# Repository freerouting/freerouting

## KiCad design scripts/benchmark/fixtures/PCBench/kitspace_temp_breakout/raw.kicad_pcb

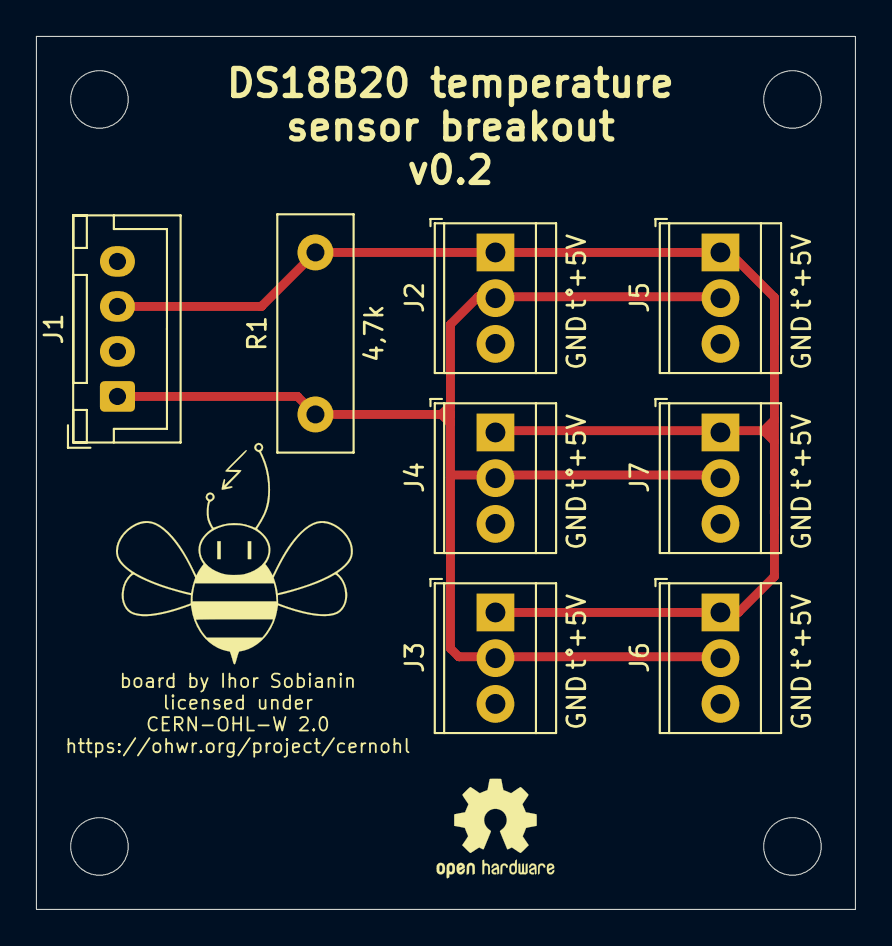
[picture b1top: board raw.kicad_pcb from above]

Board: 2 copper layers, 45.5 x 48.5 mm, 8 parts (0 on the bottom side), 3 nets.

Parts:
J1: Conn_01x04; JST_XH_B4B-XH-A_1x04_P2.50mm_Vertical
J2, J3, J4, J5, J6, J7: Conn_01x03; TerminalBlock_TE_282834-3_1x03_P2.54mm_Horizontal
R1: 4,7k; R_Box_L13.0mm_W4.0mm_P9.00mm

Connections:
+5V: J1.3, J2.1, J3.1, J4.1, J5.1, J6.1, J7.1, R1.2
GND: J1.4, J2.3, J3.3, J4.3, J5.3, J6.3, J7.3
esp_pin: J1.1, J2.2, J3.2, J4.2, J5.2, J6.2, J7.2, R1.1

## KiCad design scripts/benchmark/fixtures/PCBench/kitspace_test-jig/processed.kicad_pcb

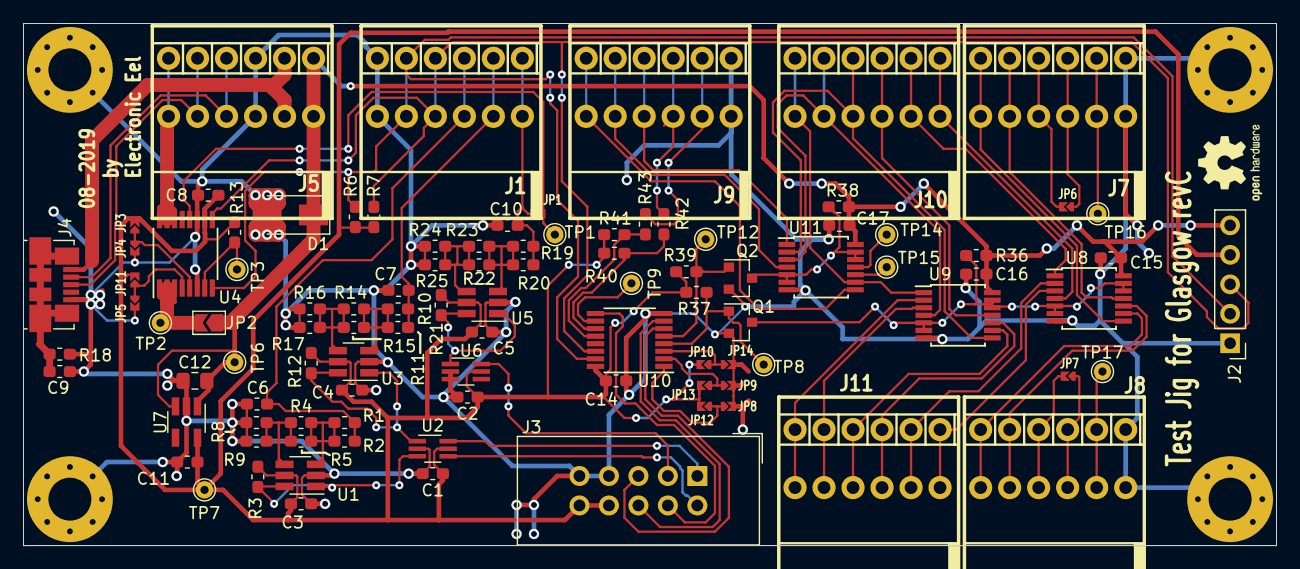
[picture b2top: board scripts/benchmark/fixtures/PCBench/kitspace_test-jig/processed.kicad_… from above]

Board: 2 copper layers, 108.0 x 45.0 mm, 103 parts (0 on the bottom side), 72 nets.

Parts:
C1, C2, C3, C4, C5, C6, C7, C8, C9, C10, C14, C15, C16, C17: 100nF; C_0603_1608Metric_Pad1.05x0.95mm_HandSolder
C11: 1µF; C_0603_1608Metric_Pad1.05x0.95mm_HandSolder
C12: 4.7µF; C_0805_2012Metric_Pad1.15x1.40mm_HandSolder
D1: SMAJ5A; D_SMA
H1, H2, H3, H4: MountingHole_Pad; MountingHole_3.7mm_Pad_Via
J1, J5, J7, J8, J9, J10, J11: AST04106; TerminalBlock_MetzConnect_AST04106_1x06_Lever_Clamp_45Degree
J2: DNP; PinHeader_1x05_P2.54mm_Vertical
J3: Conn_02x05_Odd_Even; IDC-Header_2x05_P2.54mm_Vertical
J4: USB_B_Micro; USB_Micro-B_Molex_47346-0001
JP1, JP4, JP5, JP6, JP7, JP8, JP9, JP10: SolderJumper_2_Bridged; Solderbridge-small-2pad
JP2: SolderJumper_2_Bridged; SolderJumper-2_P1.3mm_Open_TrianglePad1.0x1.5mm
JP3, JP11, JP12, JP13, JP14: SolderJumper_2_Open; Solderbridge-small-2pad
Q1, Q2: BSS138; SOT-23
R1: 5M1; R_0603_1608Metric_Pad1.05x0.95mm_HandSolder
R2: 68k; R_0603_1608Metric_Pad1.05x0.95mm_HandSolder
R3, R12, R13, R21: 4k7; R_0603_1608Metric_Pad1.05x0.95mm_HandSolder
R4, R8, R16, R22, R24, R40, R41, R42, R43: DNP; R_0603_1608Metric_Pad1.05x0.95mm_HandSolder
R5: 910R; R_0603_1608Metric_Pad1.05x0.95mm_HandSolder
R6, R7: 22k; R_0603_1608Metric_Pad1.05x0.95mm_HandSolder
R9: 33k; R_0603_1608Metric_Pad1.05x0.95mm_HandSolder
R10: 91k; R_0603_1608Metric_Pad1.05x0.95mm_HandSolder
R11: 3M6; R_0603_1608Metric_Pad1.05x0.95mm_HandSolder
R14: 1k; R_0603_1608Metric_Pad1.05x0.95mm_HandSolder
R15: 470R; R_0603_1608Metric_Pad1.05x0.95mm_HandSolder
R17: 12k; R_0603_1608Metric_Pad1.05x0.95mm_HandSolder
R18: 1M; R_0603_1608Metric_Pad1.05x0.95mm_HandSolder
R19: 510k; R_0603_1608Metric_Pad1.05x0.95mm_HandSolder
R20: 110k; R_0603_1608Metric_Pad1.05x0.95mm_HandSolder
R23: 680; R_0603_1608Metric_Pad1.05x0.95mm_HandSolder
R25: 7k5; R_0603_1608Metric_Pad1.05x0.95mm_HandSolder
R36, R38: 2k2; R_0603_1608Metric_Pad1.05x0.95mm_HandSolder
R37, R39: 100K; R_0603_1608Metric_Pad1.05x0.95mm_HandSolder
TP1, TP2, TP3, TP6, TP7, TP8, TP9, TP12, TP14, TP15, TP16, TP17: TestPoint; TestPoint_THTPad_D1.5mm_Drill0.7mm
U1, U3, U5: TPS3700; SOT-23-6_Handsoldering
U2, U6: 74LVC2G14; SOT-363_SC-70-6_Handsoldering
U4: INA260; TSSOP-16_4.4x5mm_P0.65mm
U7: AP2127K-3.3; SOT-23-5_HandSoldering
U8, U9, U11: 74HC4066; TSSOP-14_4.4x5mm_P0.65mm
U10: TCA9534; TSSOP-16_4.4x5mm_P0.65mm

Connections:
+3V3: C1.1, C2.1, C3.1, C4.1, C5.1, C8.1, C11.1, C14.1, J2.4, J3.8, J3.10, JP3.2, JP10.2, JP11.2, JP12.2, JP13.2, R3.1, R6.1, R7.1, R12.1, R13.1, R21.1, R37.1, R39.1, R40.2, R41.2, TP7.1, U1.5, U2.5, U3.5, U4.10, U5.5, U6.5, U7.5, U10.16
/DUT_Supply: J5.6, U4.14, U4.15, U4.16
/LED_1V2: J3.2, U2.4
/LED_3V3: J3.1, U2.6
/LED_5V: J3.3, U6.6
/LED_FAIL: J3.6, U10.7
/LED_PASS: J3.5, U10.6
/LED_RUN: J3.4, U10.9
/SCL: J1.4, J2.3, R7.2, U4.9, U10.14
/SDA: J1.5, J2.2, R6.2, U4.8, U10.15
/TP_1V2: C6.1, J1.3, R1.1, R2.1
/TP_3V3: C7.1, J1.2, R10.1, R11.1
/TP_5V: C10.1, J1.1, JP1.1, R19.1, R20.1
/port-connection/Aux_conn_ctrl_5V: Q2.3, R38.2, U11.5, U11.6, U11.12, U11.13
/port-connection/JIG_GPIO0: J9.3, R42.2
/port-connection/JIG_GPIO1: J9.2, R43.2
/port-connection/Port_conn_ctrl_5V: Q1.3, R36.2, U8.5, U8.6, U8.12, U8.13, U9.5, U9.6, U9.12, U9.13
/port-connection/TP_A0: J10.6, U9.1, U11.9
/port-connection/TP_A1: J10.5, U9.4, U11.3
/port-connection/TP_A2: J10.4, U9.8, U11.2
/port-connection/TP_A3: J10.3, U9.11
/port-connection/TP_A4: J10.2, U8.1
/port-connection/TP_A5: J10.1, U8.4
/port-connection/TP_A6: J7.6, U8.8
/port-connection/TP_A7: J7.5, U8.11
/port-connection/TP_A_Vio: J7.4, JP6.2
/port-connection/TP_A_Vsns: J7.3, JP6.1
/port-connection/TP_Aux_A10: J9.5, U11.4
/port-connection/TP_Aux_C9: J9.4, U11.1
/port-connection/TP_B0: J11.6, U9.2
/port-connection/TP_B1: J11.5, U9.3
/port-connection/TP_B2: J11.4, U9.9
/port-connection/TP_B3: J11.3, U9.10
/port-connection/TP_B4: J11.2, U8.2
/port-connection/TP_B5: J11.1, U8.3
/port-connection/TP_B6: J8.6, U8.9
/port-connection/TP_B7: J8.5, U8.10
/port-connection/TP_B_Vio: J8.4, JP7.2
/port-connection/TP_B_Vsns: J8.3, JP7.1
/port-connection/TP_Sync: J9.6, U11.8
/port-connection/~Aux_conn_ctrl: Q2.1, R39.2, TP12.1, U10.5
/port-connection/~Port_conn_ctrl: Q1.1, R37.2, TP8.1, U10.4
GND: C1.2, C2.2, C3.2, C4.2, C5.2, C6.2, C7.2, C8.2, C9.2, C10.2, C11.2, C12.2, C14.2, C15.2, C16.2, C17.2, D1.2, H1.1, H2.1, H3.1, H4.1, J1.6, J2.1, J3.7, J3.9, J4.5, J5.3, J7.1, J8.1, J9.1, JP4.2, JP5.2, JP8.2, JP9.2, JP14.2, Q1.2, Q2.2, R8.2, R9.2, R16.2, R17.2, R18.2, R24.2, R25.2, U1.2, U2.2, U3.2, U4.6, U4.11, U5.2, U6.2, U6.3, U7.2, U8.7, U9.7, U10.8, U11.7
unnamed: C9.1, J4.6, R18.1
unnamed: J4.1, J5.2
unnamed: J4.2, J5.4
unnamed: J4.3, J5.5
unnamed: J7.2, TP16.1
unnamed: J8.2, TP17.1
unnamed: JP1.2, TP1.1, U4.12
unnamed: JP2.2, TP2.1, U4.1, U4.2, U4.3
unnamed: JP3.1, JP4.1, U4.5
unnamed: JP10.1, JP14.1, U10.3
unnamed: JP5.1, JP11.1, U4.4
unnamed: JP8.1, JP12.1, U10.1
unnamed: JP9.1, JP13.1, U10.2
unnamed: R1.2, R2.2, R4.1, R5.1, U1.3
unnamed: R3.2, U1.1, U1.6, U2.3
unnamed: R4.2, R5.2, R8.1, R9.1, U1.4
unnamed: R10.2, R11.2, R14.1, R15.1, U3.3
unnamed: R12.2, U2.1, U3.1, U3.6
unnamed: R13.2, TP3.1, U4.7
unnamed: R14.2, R15.2, R16.1, R17.1, U3.4
unnamed: R19.2, R20.2, R22.1, R23.1, U5.3
unnamed: R21.2, U5.1, U5.6, U6.1
unnamed: R22.2, R23.2, R24.1, R25.1, U5.4
unnamed: R40.1, R42.1, U10.11
unnamed: R41.1, R43.1, U10.12
unnamed: TP9.1, U10.10
unnamed: TP14.1, U11.11
unnamed: TP15.1, U11.10
VBUS: C12.1, C15.1, C16.1, C17.1, D1.1, J2.5, J5.1, JP2.1, R36.1, R38.1, TP6.1, U7.1, U7.3, U8.14, U9.14, U11.14

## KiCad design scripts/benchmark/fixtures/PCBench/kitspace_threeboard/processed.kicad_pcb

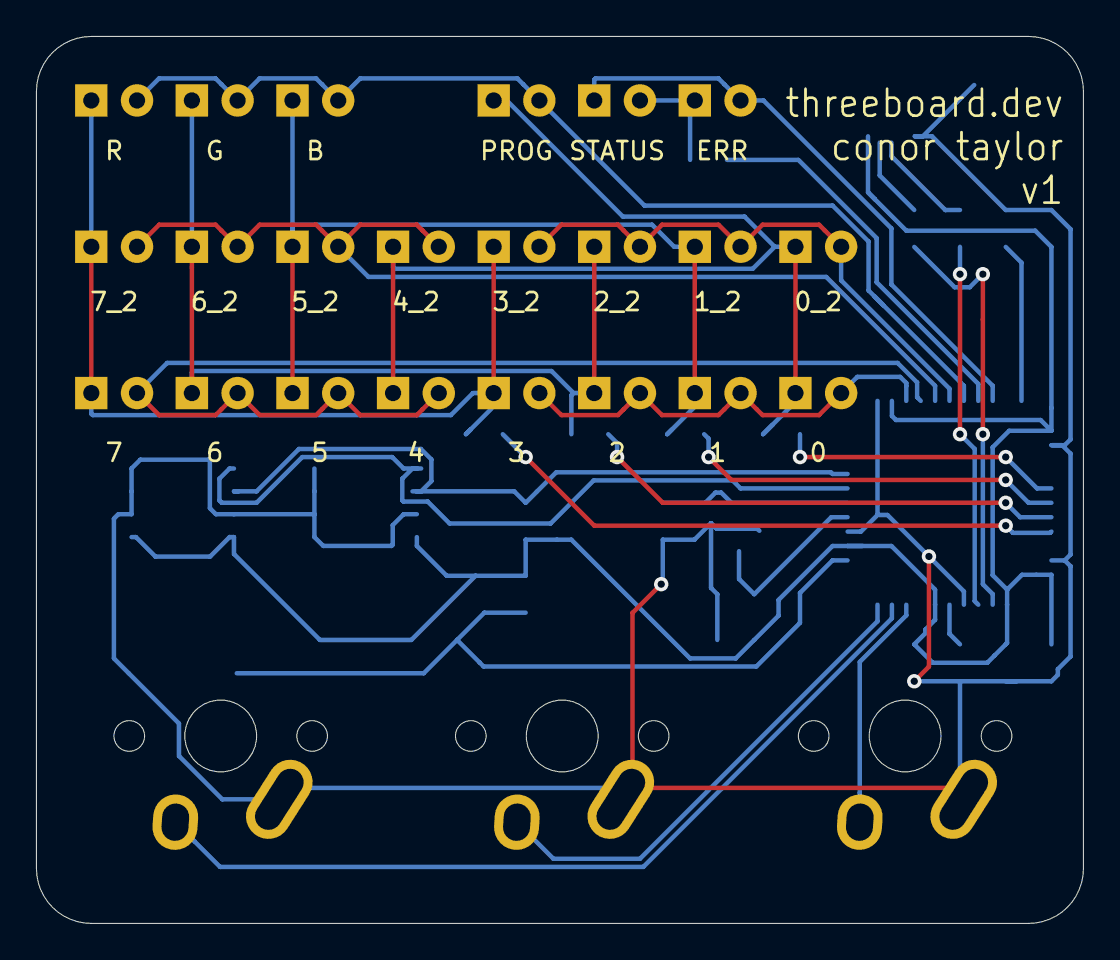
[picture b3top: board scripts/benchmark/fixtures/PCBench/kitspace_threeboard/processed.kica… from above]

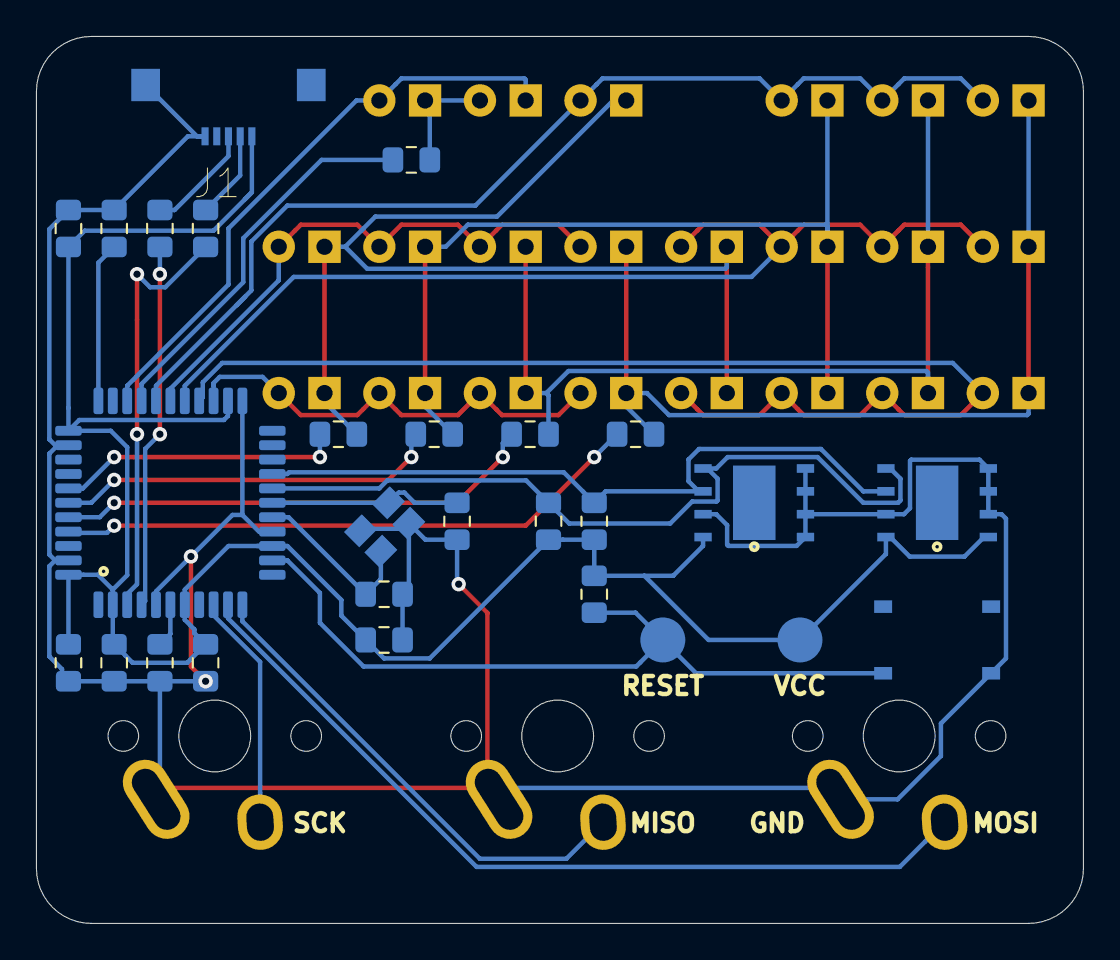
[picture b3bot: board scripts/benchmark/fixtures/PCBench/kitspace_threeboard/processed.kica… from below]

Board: 2 copper layers, 58.2 x 49.3 mm, 50 parts (25 on the bottom side), 32 nets.

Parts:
0, 0_2, 1, 1_2, 2, 2_2, 3, 3_2, 4, 4_2, 5, 5_2, 6, 6_2, 7, 7_2: LED; LED_D3.0mm
B: LED; LED_D3.0mm
C1, C2: 22p; C_0805_2012Metric_Pad1.15x1.40mm_HandSolder
C3, C4, C5, C6: 0.1u; C_0805_2012Metric_Pad1.15x1.40mm_HandSolder
C7: 4.7u; C_0805_2012Metric_Pad1.15x1.40mm_HandSolder
C8: 1u; C_0805_2012Metric_Pad1.15x1.40mm_HandSolder
ERR: LED; LED_D3.0mm
G: LED; LED_D3.0mm
J1: USB_mini_micro_B; GCT_USB3070-XX-X_REVE
K1, K2, K3: KEYSW; Mx_Alps_100
PROG: LED; LED_D3.0mm
R: LED; LED_D3.0mm
R1, R2: 10k; R_0805_2012Metric_Pad1.15x1.40mm_HandSolder
R3, R4: 22; R_0805_2012Metric_Pad1.15x1.40mm_HandSolder
R5, R6, R7, R8, R9: 220; R_0805_2012Metric_Pad1.15x1.40mm_HandSolder
R10, R11: 4.7k; R_0805_2012Metric_Pad1.15x1.40mm_HandSolder
STATUS: LED; LED_D3.0mm
SW1: SW_PUSH; SW_PTS526_SK08_SMTR2_LFS
U1: ATMEGA32U4; LQFP-44_10x10mm_P0.8mm
U2, U3: 24LC512; DFN500X600X95-9N
X1: XTAL_GND; crystal_FA238-TSX3225

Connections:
/col0: R5.2, U1.41
/col1: R6.2, U1.40
/col2: R7.2, U1.39
/col3: R8.2, U1.38
/eeprom_scl: R11.2, U1.19, U2.6, U3.6
/eeprom_sda: R10.2, U1.18, U2.5, U3.5
/row0: 4_2.2, 5_2.2, 6_2.2, 7_2.2, U1.27
/row1: 0_2.2, 1_2.2, 2_2.2, 3_2.2, U1.28
/row2: 4.2, 5.2, 6.2, 7.2, U1.26
/row3: 0.2, 1.2, 2.2, 3.2, U1.25
/row4: B.2, G.2, PROG.2, R.2, U1.29
/status0: R9.2, U1.30
/status1: ERR.2, STATUS.1, U1.31
/switch1: K1.2, U1.10
/switch2: K2.2, U1.11
/switch3: K3.2, U1.9
GND: C1.2, C2.2, C3.2, C4.2, C5.2, C6.2, C7.2, C8.2, J1.5, J1.6, K1.1, K2.1, K3.1, R2.1, SW1.1, U1.5, U1.15, U1.23, U1.35, U1.43, U2.2, U2.3, U2.4, U2.7, U3.1, U3.2, U3.3, U3.4, U3.7, X1.3
unnamed: C1.1, U1.16, X1.1
unnamed: C2.1, U1.17, X1.2
unnamed: C8.1, U1.6
unnamed: 3.1, 3_2.1, 7.1, 7_2.1, R.1, R5.1
unnamed: 2.1, 2_2.1, 6.1, 6_2.1, G.1, R6.1
unnamed: 1.1, 1_2.1, 5.1, 5_2.1, B.1, R7.1
unnamed: 0.1, 0_2.1, 4.1, 4_2.1, PROG.1, R8.1
unnamed: ERR.1, R9.1, STATUS.2
unnamed: J1.2, R3.2
unnamed: J1.3, R4.2
unnamed: R1.2, SW1.2, U1.13
unnamed: R2.2, U1.33
unnamed: R3.1, U1.3
unnamed: R4.1, U1.4
VCC: C3.1, C4.1, C5.1, C6.1, C7.1, J1.1, R1.1, R10.1, R11.1, U1.2, U1.7, U1.14, U1.24, U1.34, U1.44, U2.1, U2.8, U3.8

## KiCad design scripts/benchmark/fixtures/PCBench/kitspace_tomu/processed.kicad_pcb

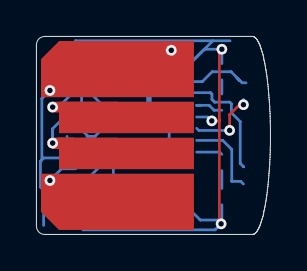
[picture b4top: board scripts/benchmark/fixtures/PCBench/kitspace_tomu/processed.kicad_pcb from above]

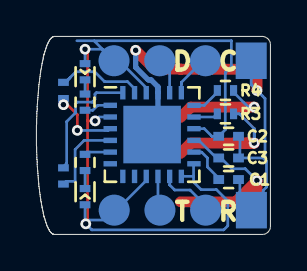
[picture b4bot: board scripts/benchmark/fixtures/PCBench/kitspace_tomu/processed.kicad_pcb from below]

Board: 2 copper layers, 13.0 x 11.0 mm, 15 parts (14 on the bottom side), 20 nets.

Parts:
C1, C2: 1uF; C_0402
C3: 47uF; C_0402
D1, D2: LED; LED_0402
P1: USART0; debug-points
P2: DEBUG; debug-points
P3: USB-PCB
R1, R2: 75; R_0402
R3, R4: 15; R_0402
U1: EFM32HG309; QFN-24-1EP_5x5mm_Pitch0.65mm
W1: CAP0; minimal-points
W2: CAP1; minimal-points

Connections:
+3V3: C2.1, D1.2, D2.2, P1.4, P2.4, U1.2, U1.9, U1.12, U1.13, U1.16, U1.22
/CAP0A: U1.3, W1.2
/CAP0B: U1.23, W1.1
/CAP1A: U1.4, W2.2
/CAP1B: U1.24, W2.1
/DBG_SWCLK: P2.2, U1.19
/DBG_SWDIO: P2.3, U1.20
/DEC: C1.2, U1.14
/LED0: R2.2, U1.5
/LED1: R1.1, U1.1
/LEU0_RX: P1.2, U1.11
/LEU0_TX: P1.3, U1.10
/RUSB_D+: R4.2, U1.18
/RUSB_D-: R3.2, U1.17
/USB_5V: C3.1, P3.1, U1.15
/USB_D+: P3.3, R4.1
/USB_D-: P3.2, R3.1
GND: C1.1, C2.2, C3.2, P1.1, P2.1, P3.4, U1.21, U1.25
unnamed: D1.1, R1.2
unnamed: D2.1, R2.1

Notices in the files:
scripts/benchmark/fixtures/PCBench/kitspace_temp_breakout/raw.kicad_pcb:
licensed under
CERN-OHL-W 2.0
scripts/benchmark/fixtures/PCBench/kitspace_tomu/processed.kicad_pcb:
License: CC-BY-SA 4.0 or TAPR
